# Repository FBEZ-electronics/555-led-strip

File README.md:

# 555-led-strip
Led strip dimmer based on NE555

* [Schematics](https://kicanvas.org/?github=https%3A%2F%2Fgithub.com%2FFBEZ%2F555-led-strip%2Fblob%2Fmain%2F555-led-strip-dimmer%2F555-led-strip-dimmer.kicad_sch)
* [PCB](https://kicanvas.org/?github=https%3A%2F%2Fgithub.com%2FFBEZ%2F555-led-strip%2Fblob%2Fmain%2F555-led-strip-dimmer%2F555-led-strip-dimmer.kicad_pcb)

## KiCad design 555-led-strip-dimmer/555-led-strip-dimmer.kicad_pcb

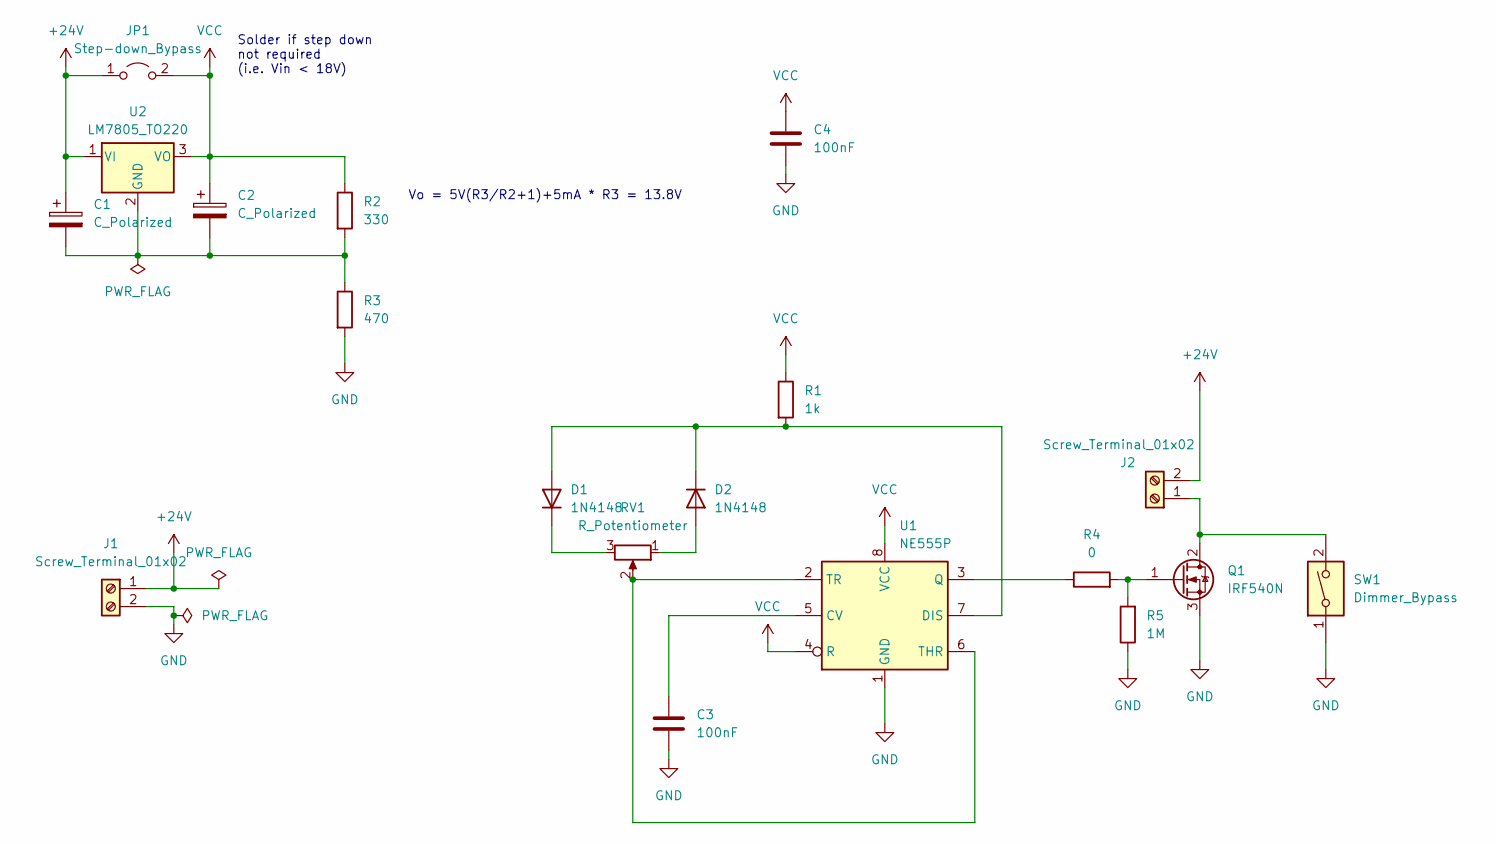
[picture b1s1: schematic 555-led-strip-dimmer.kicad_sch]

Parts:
C1, C2: C_Polarized; CP_Radial_D8.0mm_P5.00mm
C3, C4: 100nF; C_Rect_L7.0mm_W2.5mm_P5.00mm
D1, D2: 1N4148; D_DO-35_SOD27_P7.62mm_Horizontal
J1, J2: Screw_Terminal_01x02; TerminalBlock_Phoenix_PT-1,5-2-5.0-H_1x02_P5.00mm_Horizontal
JP1: Step-down_Bypass; TestPoint_2Pads_Pitch2.54mm_Drill0.8mm
Q1: IRF540N; TO-220-3_Vertical
R1: 1k; R_Axial_DIN0411_L9.9mm_D3.6mm_P12.70mm_Horizontal
R2: 330; R_Axial_DIN0411_L9.9mm_D3.6mm_P12.70mm_Horizontal
R3: 470; R_Axial_DIN0411_L9.9mm_D3.6mm_P12.70mm_Horizontal
R4: 0; R_Axial_DIN0411_L9.9mm_D3.6mm_P12.70mm_Horizontal
R5: 1M; R_Axial_DIN0411_L9.9mm_D3.6mm_P12.70mm_Horizontal
RV1: R_Potentiometer; Potentiometer_ACP_CA14-H4_Horizontal
SW1: Dimmer_Bypass; PinHeader_2x01_P2.54mm_Vertical
U1: NE555P; DIP-8_W7.62mm
U2: LM7805_TO220; TO-220-3_Vertical

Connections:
+24V: C1.1, J1.1, J2.2, JP1.1 (A), U2.1 (VI)
GND: C3.2, C4.2, J1.2, Q1.3 (S), R3.2, R5.1, SW1.1, U1.1 (GND)
unnamed: D1.2 (A), D2.1 (K), R1.2, U1.7 (DIS)
unnamed: D1.1 (K), RV1.3
unnamed: D2.2 (A), RV1.1
unnamed: J2.1, Q1.2 (D), SW1.2
unnamed: Q1.1 (G), R4.2, R5.2
unnamed: C3.1, U1.5 (CV)
unnamed: R4.1, U1.3 (Q)
unnamed: RV1.2, U1.2 (TR), U1.6 (THR)
unnamed: C1.2, C2.2, R2.2, R3.1, U2.2 (GND)
VCC: C2.1, C4.1, JP1.2 (B), R1.1, R2.1, U1.4 (R), U1.8 (VCC), U2.3 (VO)

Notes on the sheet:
Vo = 5V(R3/R2+1)+5mA * R3 = 13.8V
Solder if step down not required (i.e. Vin < 18V)

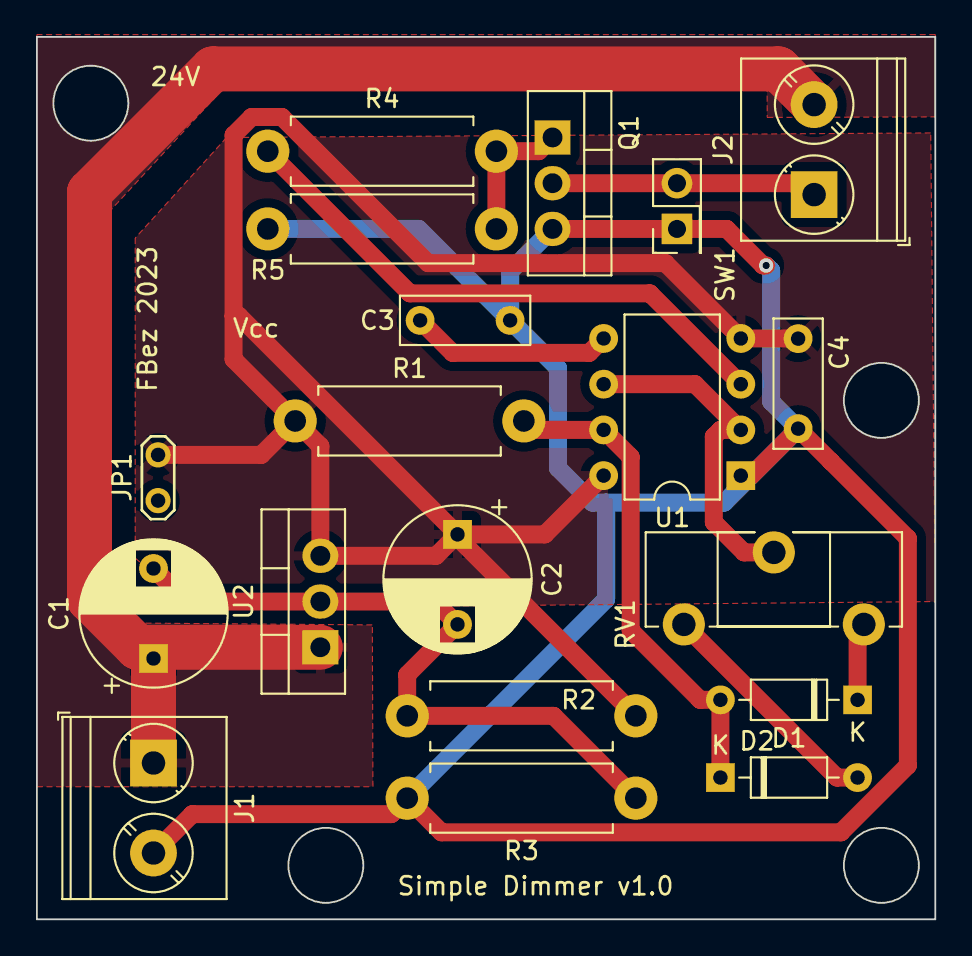
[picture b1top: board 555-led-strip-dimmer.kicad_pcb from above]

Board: 2 copper layers, 49.9 x 49.0 mm, 19 parts (0 on the bottom side), 12 nets.

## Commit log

2023-11-26 added files
